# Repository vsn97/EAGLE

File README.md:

# EAGLE PCB Design  

Hey everyone! Started off the introduction of PCB Design and these are the few board schematics and boards I have designed and developed.

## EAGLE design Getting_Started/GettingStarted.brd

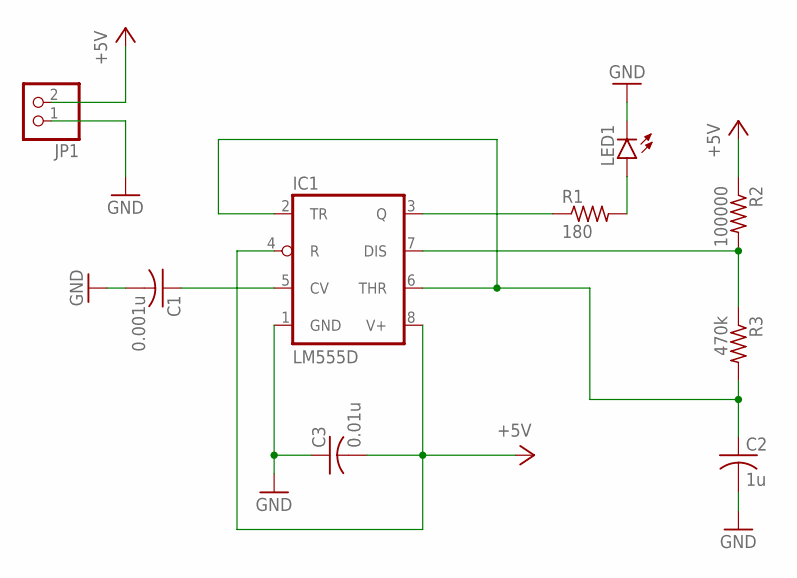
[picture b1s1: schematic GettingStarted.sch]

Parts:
C1: 0.001u; C0805
C2: 1u; C0805
C3: 0.01u; C0805
IC1: LM555D; SO08
JP1: PINHD-1X2; 1X02
LED1: LED5MM
R1: 180; R0805
R2: 100000; R0805
R3: 470k; R0805

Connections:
+5V: C3.2, IC1.4 (R), IC1.8 (V+), JP1.2, R2.1
GND: C1.2, C2.2, C3.1, IC1.1 (GND), JP1.1, LED1.K (C)
unnamed: IC1.3 (Q), R1.1
unnamed: IC1.7 (DIS), R2.2, R3.1
unnamed: C2.1, IC1.2 (TR), IC1.6 (THR), R3.2
unnamed: LED1.A, R1.2
unnamed: C1.1, IC1.5 (CV)

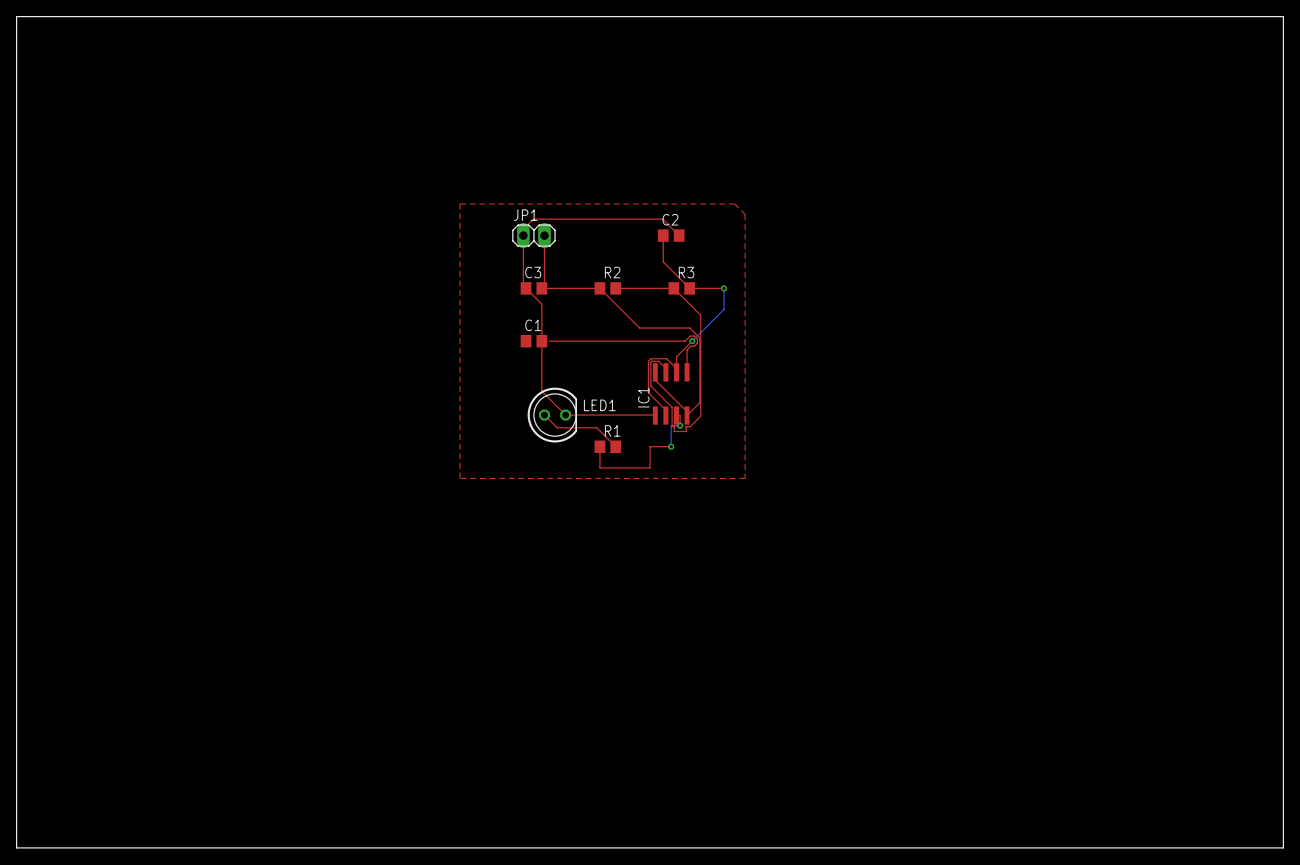
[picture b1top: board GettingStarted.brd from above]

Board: 2 copper layers, 152.4 x 100.0 mm, 9 parts (0 on the bottom side), 7 nets.

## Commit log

2019-09-06 Create LICENSE
2019-09-06 Getting Started Project
